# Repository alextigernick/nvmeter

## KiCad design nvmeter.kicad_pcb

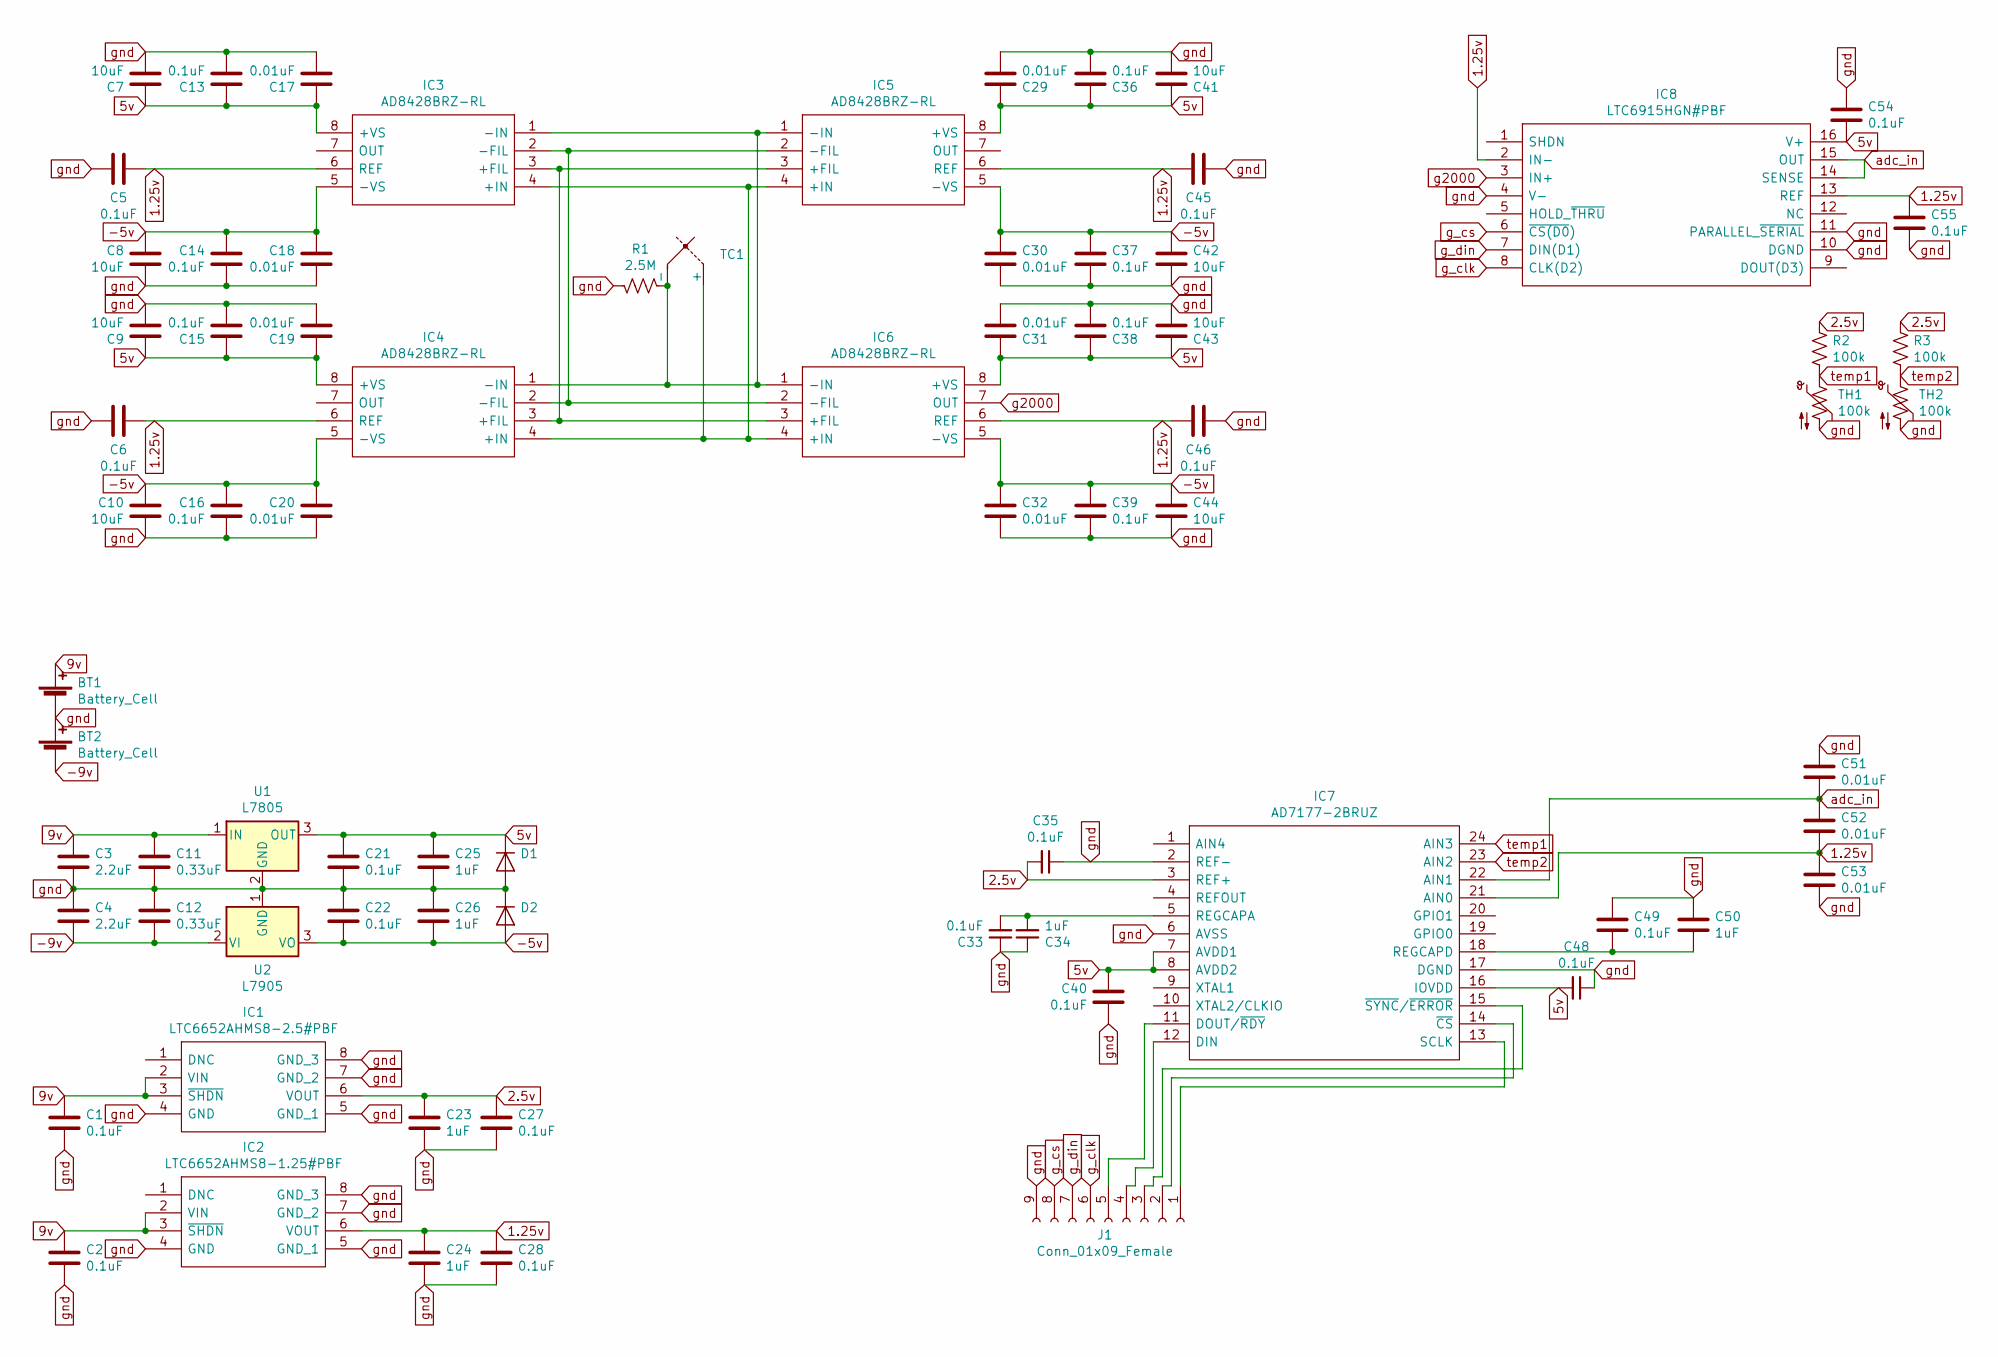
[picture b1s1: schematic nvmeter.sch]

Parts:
BT1, BT2: Battery_Cell; xt60_wire holes
C1, C2, C5, C6, C13, C14, C15, C16, C21, C22, C27, C28, C33, C35, C36, C37, C38, C39, C40, C45, C46, C48, C49, C54, C55: 0.1uF; C_0603_1608Metric_Pad1.05x0.95mm_HandSolder
C3, C4: 2.2uF; C_1206_3216Metric_Pad1.42x1.75mm_HandSolder
C7, C8, C9, C10, C41, C42, C43, C44: 10uF; C_1206_3216Metric_Pad1.42x1.75mm_HandSolder
C11, C12: 0.33uF; C_1206_3216Metric_Pad1.42x1.75mm_HandSolder
C17, C18, C19, C20, C29, C30, C31, C32, C51, C52, C53: 0.01uF; C_0603_1608Metric_Pad1.05x0.95mm_HandSolder
C23, C24, C25, C26, C34, C50: 1uF; C_0805_2012Metric_Pad1.15x1.40mm_HandSolder
D1, D2: SOD-523
IC1: LTC6652AHMS8-2.5#PBF; MSOP-8_3x3mm_P0.65mm; Manufacturer_Part_Number LTC6652AHMS8-2.5#PBF
IC2: LTC6652AHMS8-1.25#PBF; MSOP-8_3x3mm_P0.65mm; Manufacturer_Part_Number LTC6652AHMS8-1.25#PBF
IC3, IC4, IC5, IC6: AD8428BRZ-RL; SOIC-8_3.9x4.9mm_P1.27mm; Manufacturer_Part_Number AD8428BRZ-RL; Mouser Part Number 584-AD8428BRZ-R
IC7: AD7177-2BRUZ; SOP65P640X120-24N; Manufacturer_Part_Number AD7177-2BRUZ; Mouser Part Number 584-AD7177-2BRUZ
IC8: LTC6915HGN#PBF; SSOP-16_3.9x4.9mm_P0.635mm; Manufacturer_Part_Number LTC6915HGN#PBF; Mouser Part Number 584-LTC6915HGN#PBF
J1: Conn_01x09_Female; Pin_Header_Straight_1x09_Pitch2.54mm
R1: 2.5M; R_0805_2012Metric_Pad1.15x1.40mm_HandSolder
R2, R3: 100k; R_0805_2012Metric_Pad1.15x1.40mm_HandSolder
TC1: Pin_Header_Straight_1x02_Pitch1.00mm
TH1, TH2: 100k; Pin_Header_Straight_1x02_Pitch2.54mm
U1: L7805; TO-263-2
U2: L7905; TO-263-2

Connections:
1.25v: C5.1, C6.1, C24.1, C28.1, C45.1, C46.1, C52.2, C53.1, C55.1, IC2.6 (VOUT), IC3.6 (REF), IC4.6 (REF), IC5.6 (REF), IC6.6 (REF), IC7.21 (AIN0), IC8.2 (IN-), IC8.13 (REF)
2.5v: C23.1, C27.1, C35.2, IC1.6 (VOUT), IC7.3 (REF+), R2.1, R3.1
5v: C7.1, C9.1, C13.1, C15.1, C17.1, C19.1, C21.1, C25.1, C29.1, C31.1, C36.1, C38.1, C40.1, C41.1, C43.1, C48.2, C54.2, D1.1 (K), IC3.8 (+VS), IC4.8 (+VS), IC5.8 (+VS), IC6.8 (+VS), IC7.7 (AVDD1), IC7.8 (AVDD2), IC7.16 (IOVDD), IC8.16 (V+), U1.3 (OUT)
9v: BT1.1 (+), C1.1, C2.1, C3.1, C11.1, IC1.2 (VIN), IC1.3 (~SHDN), IC2.2 (VIN), IC2.3 (~SHDN), U1.1 (IN)
-5v: C8.1, C10.1, C14.1, C16.1, C18.1, C20.1, C22.2, C26.2, C30.1, C32.1, C37.1, C39.1, C42.1, C44.1, D2.2 (A), IC3.5 (-VS), IC4.5 (-VS), IC5.5 (-VS), IC6.5 (-VS), U2.3 (VO)
-9v: BT2.2 (-), C4.2, C12.2, U2.2 (VI)
unnamed: C33.2, C34.2, IC7.5 (REGCAPA)
unnamed: C49.2, C50.2, IC7.18 (REGCAPD)
unnamed: IC3.1 (-IN), IC4.1 (-IN), IC5.1 (-IN), IC6.1 (-IN), R1.2, TC1.2 (-)
unnamed: IC3.2 (-FIL), IC4.2 (-FIL), IC5.2 (-FIL), IC6.2 (-FIL)
unnamed: IC3.3 (+FIL), IC4.3 (+FIL), IC5.3 (+FIL), IC6.3 (+FIL)
unnamed: IC3.4 (+IN), IC4.4 (+IN), IC5.4 (+IN), IC6.4 (+IN), TC1.1 (+)
unnamed: IC7.11 (DOUT/~RDY), J1.5
unnamed: IC7.12 (DIN), J1.4
unnamed: IC7.13 (SCLK), J1.1
unnamed: IC7.14 (~CS), J1.2
unnamed: IC7.15 (~SYNC~/~ERROR), J1.3
adc_in: C51.2, C52.1, IC7.22 (AIN1), IC8.14 (SENSE), IC8.15 (OUT)
g2000: IC6.7 (OUT), IC8.3 (IN+)
g_clk: IC8.8 (CLK(D2)), J1.6
g_cs: IC8.6 (~CS(D0)), J1.8
g_din: IC8.7 (DIN(D1)), J1.7
gnd: BT1.2 (-), BT2.1 (+), C1.2, C2.2, C3.2, C4.1, C5.2, C6.2, C7.2, C8.2, C9.2, C10.2, C11.2, C12.1, C13.2, C14.2, C15.2, C16.2, C17.2, C18.2, C19.2, C20.2, C21.2, C22.1, C23.2, C24.2, C25.2, C26.1, C27.2, C28.2, C29.2, C30.2, C31.2, C32.2, C33.1, C34.1, C35.1, C36.2, C37.2, C38.2, C39.2, C40.2, C41.2, C42.2, C43.2, C44.2, C45.2, C46.2, C48.1, C49.1, C50.1, C51.1, C53.2, C54.1, C55.2, D1.2 (A), D2.1 (K), IC1.4 (GND), IC1.5 (GND_1), IC1.7 (GND_2), IC1.8 (GND_3), IC2.4 (GND), IC2.5 (GND_1), IC2.7 (GND_2), IC2.8 (GND_3), IC7.2 (REF-), IC7.6 (AVSS), IC7.17 (DGND), IC8.4 (V-), IC8.10 (DGND), IC8.11 (PARALLEL_~SERIAL), J1.9, R1.1, TH1.2, TH2.2, U1.2 (GND), U2.1 (GND)
temp1: IC7.24 (AIN3), R2.2, TH1.1
temp2: IC7.23 (AIN2), R3.2, TH2.1

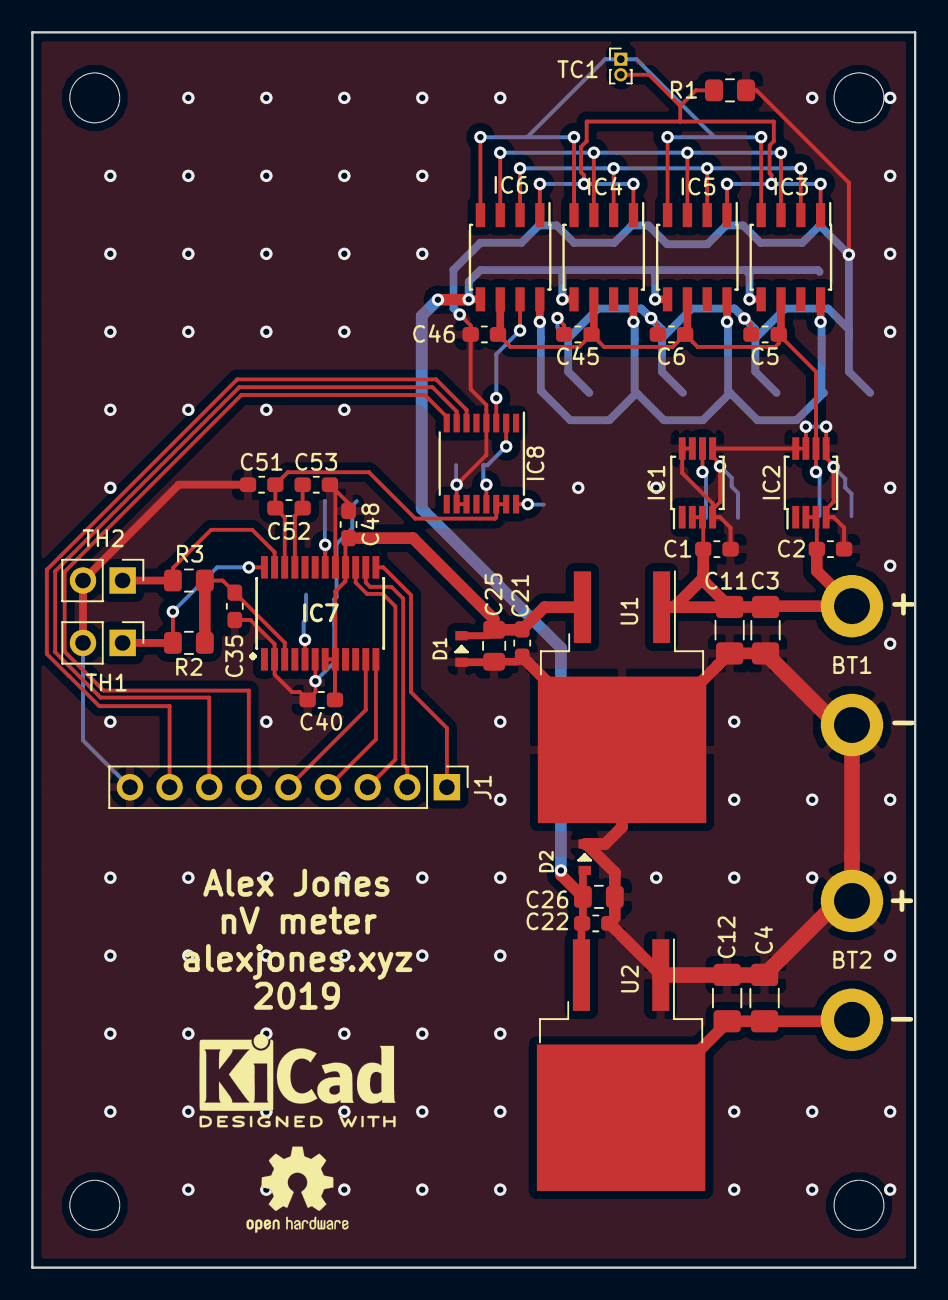
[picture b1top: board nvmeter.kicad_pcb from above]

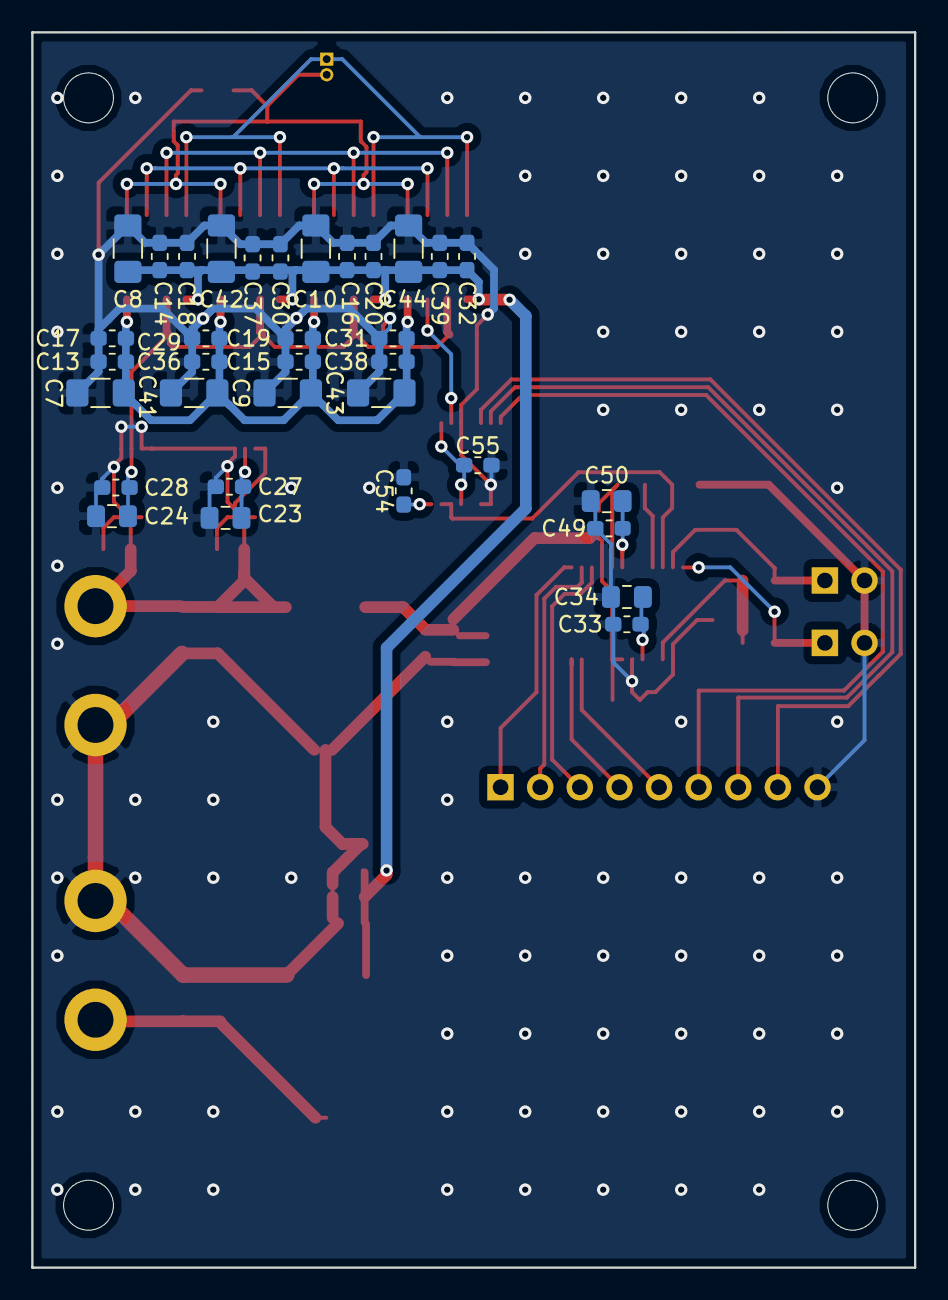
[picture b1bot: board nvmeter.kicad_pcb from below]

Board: 2 copper layers, 56.6 x 79.2 mm, 75 parts (34 on the bottom side), 25 nets.

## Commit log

2019-10-16 initial
